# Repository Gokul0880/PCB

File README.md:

View this project on [CADLAB.io](https://cadlab.io/project/28970). 

# PCB Projects

## Overview
This repository contains various PCB designs created using KiCad as part of my learning journey. The projects include different types of power converters, sensor modules, and other embedded system circuits.

## Included Designs
- **Buck Converter** - Step-down DC-DC converter
- **Boost Converter** - Step-up DC-DC converter
- **Linear Regulators** - Voltage regulation circuits
- **Power Management Circuits** - Various power distribution designs
- **Sensor Modules** - PCB layouts for different sensors

## Project Structure
```
📂 project_root/
 ├── 📁 buck_converter/   # Buck converter design files
 ├── 📁 boost_converter/  # Boost converter design files
 ├── 📁 regulators/       # Linear regulator PCB files
 ├── 📁 sensor_modules/   # Various sensor module PCB designs
 ├── 📁 gerber_files/     # Manufacturing-ready Gerber files
 ├── 📁 bom/              # Bill of Materials (BOM)
 ├── 📁 3d_models/        # 3D models for components
 ├── 📁 documentation/    # Datasheets, design notes, etc.
 ├── README.md           # Project overview (this file)
```

## Installation & Usage
1. Clone the repository:
   ```sh
   git clone https://github.com/yourusername/your-pcb-repo.git
   ```
2. Open the project in KiCad:
   - Open KiCad and load the required `.pro` file.
   - Access the schematic editor and PCB layout as needed.
3. Generate Gerber files for manufacturing:
   - Use KiCad's "Plot" function to export Gerber files.

## Bill of Materials (BOM)
Each project folder contains a BOM listing all components used in the design.

## Contribution
Feel free to fork this repository and submit pull requests for improvements or modifications.

## License
This project is licensed under the MIT License - see the LICENSE file for details.

## Author
Gokula Kannan R

For any questions or collaborations, contact me at [gokul567gd@gmail.com].

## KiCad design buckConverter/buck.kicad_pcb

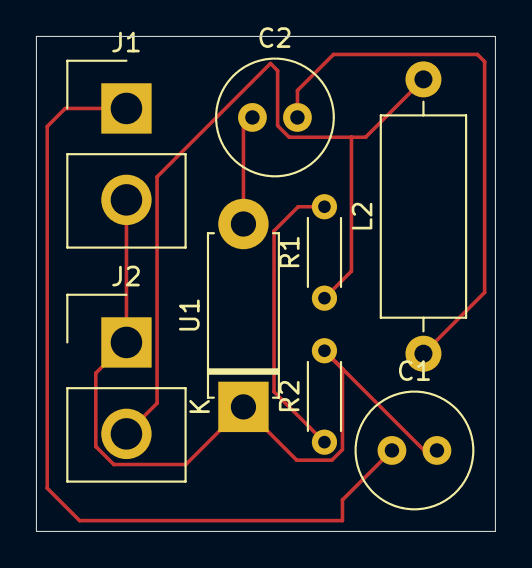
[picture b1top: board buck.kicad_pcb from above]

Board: 2 copper layers, 25.5 x 27.5 mm, 8 parts (0 on the bottom side), 6 nets.

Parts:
C1: C; C_Radial_D6.3mm_H5.0mm_P2.50mm
C2: C; C_Radial_D6.3mm_H11.0mm_P2.50mm
J1, J2: IN; Samtec_HPM-02-01-x-S_Straight_1x02_Pitch5.08mm
L2: SPM3015T-4R7M-LR; L_Axial_L11.0mm_D4.5mm_P15.24mm_Horizontal_Fastron_MECC
R1, R2: R_US; R_Axial_DIN0204_L3.6mm_D1.6mm_P5.08mm_Horizontal
U1: TPS561208DDCR; D_5W_P10.16mm_Horizontal

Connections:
/IN: C1.1, J1.1
/VBST: C2.1, U1.2 (SW)
GND: C1.2, J1.2, J2.1, R2.2, U1.1 (GND)
unnamed: C2.2, L2.1
unnamed: J2.2, L2.2, R1.1
unnamed: R1.2, R2.1

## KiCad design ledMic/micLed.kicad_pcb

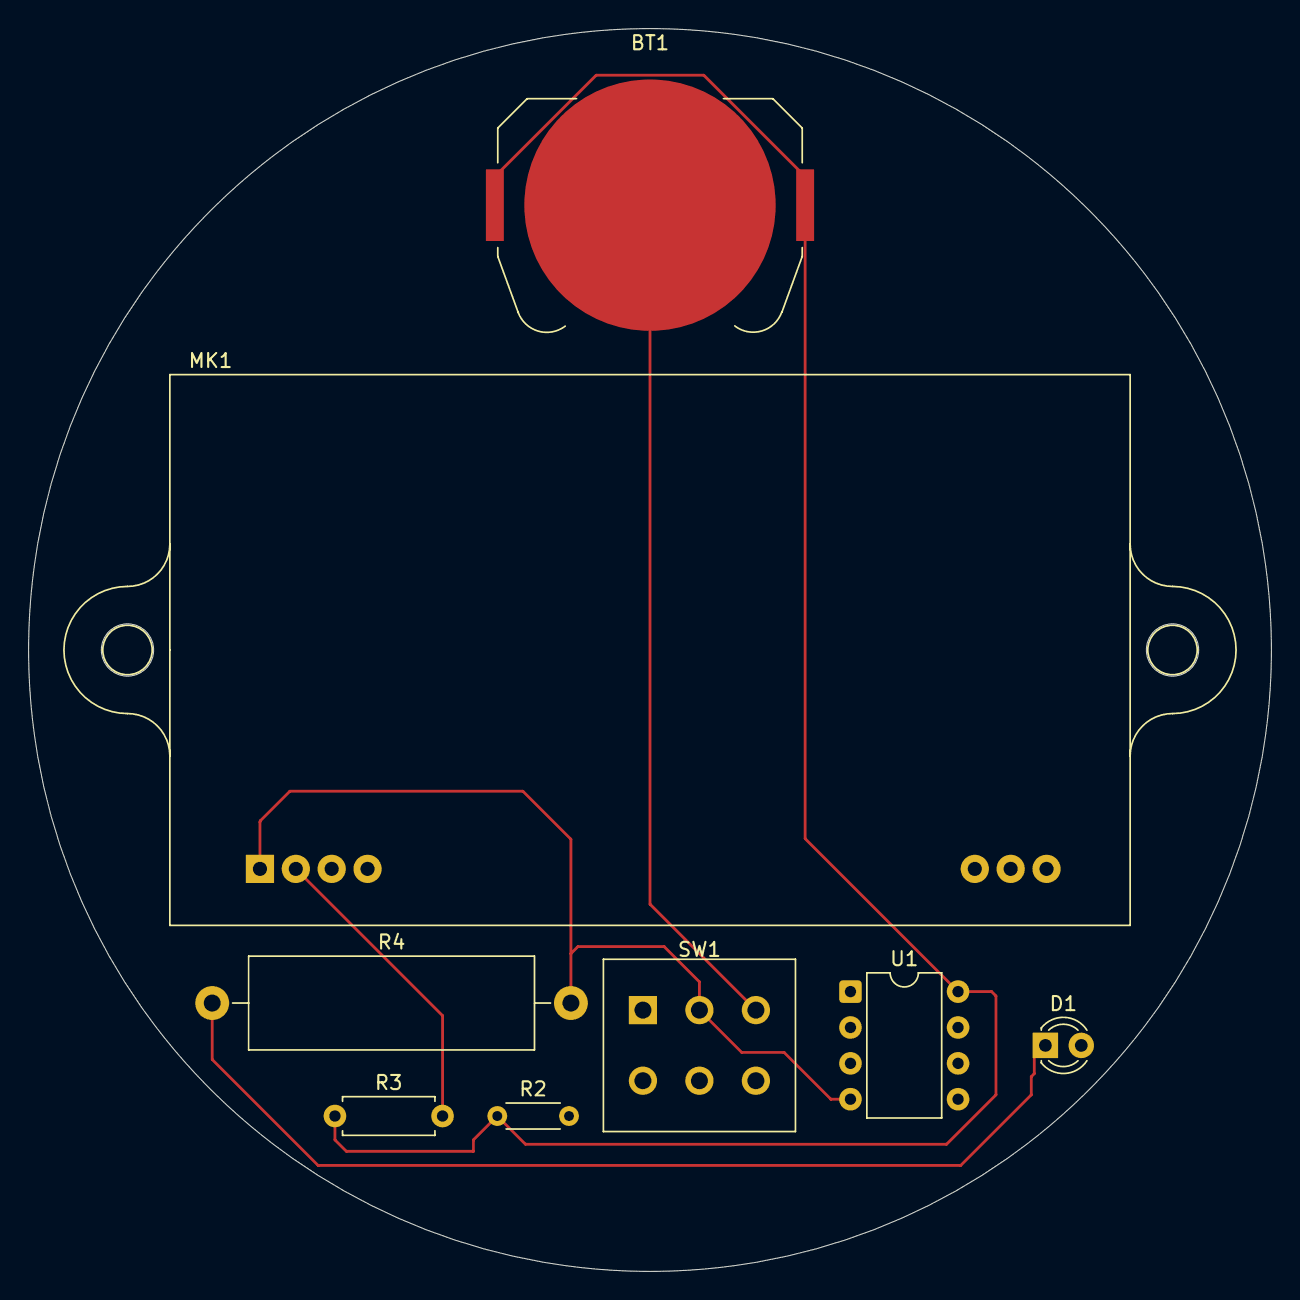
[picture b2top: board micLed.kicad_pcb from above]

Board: 2 copper layers, 88.0 x 88.0 mm, 8 parts (0 on the bottom side), 5 nets.

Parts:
BT1: 3.3v cell; BatteryHolder_Keystone_3034_1x20mm
D1: LED; LED_D3.0mm_Clear
MK1: Microphone; Reverb_BTDR-1H
R2: 10k; R_Axial_DIN0204_L3.6mm_D1.6mm_P5.08mm_Horizontal
R3: R; R_Axial_DIN0207_L6.3mm_D2.5mm_P7.62mm_Horizontal
R4: 470; R_Axial_Power_L20.0mm_W6.4mm_P25.40mm
SW1: SW_DPDT_x2; SW_PUSH_E-Switch_FS5700DP_DPDT
U1: ATtiny85V-10P; DIP-8_W7.62mm

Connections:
GND: MK1.1 (-), R4.2, SW1.2 (B), U1.4 (GND)
unnamed: BT1.2 (-), SW1.3 (C)
unnamed: D1.1 (K), R4.1
unnamed: MK1.2 (+), R3.2
VCC: BT1.1 (+), R2.1, R3.1, U1.8 (VCC)

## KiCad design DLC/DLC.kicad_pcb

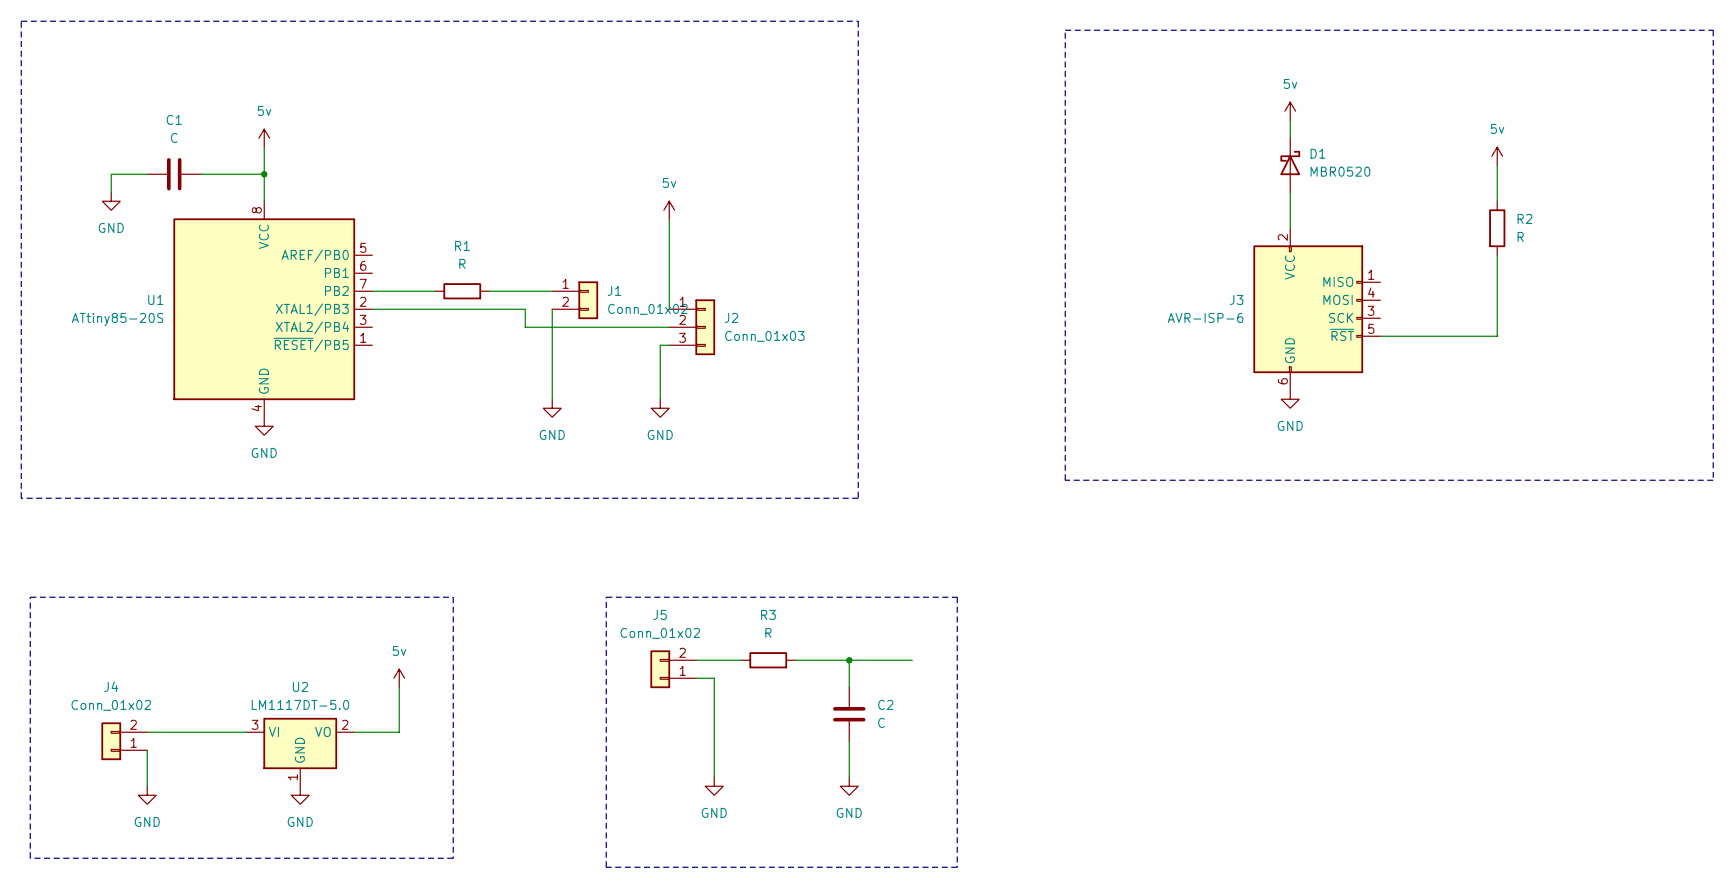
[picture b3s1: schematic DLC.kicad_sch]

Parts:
C1, C2: C; C_Axial_L5.1mm_D3.1mm_P12.50mm_Horizontal
D1: MBR0520; D_SOD-123
J1, J4, J5: Conn_01x02; PinHeader_1x02_P2.54mm_Horizontal
J2: Conn_01x03; PinHeader_1x03_P2.54mm_Horizontal
J3: AVR-ISP-6; IDC-Header_2x03_P2.54mm_Horizontal
R1, R2, R3: R; R_Axial_DIN0207_L6.3mm_D2.5mm_P7.62mm_Horizontal
U1: ATtiny85-20S; SOIC-8_5.3x5.3mm_P1.27mm
U2: LM1117DT-5.0; TO-252-3_TabPin2

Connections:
5v: C1.2, D1.1 (K), J2.1, R2.1, U1.8 (VCC), U2.2 (VO)
GND: C1.1, C2.2, J1.2, J2.3, J3.6 (GND), J4.1, J5.1, U1.4 (GND), U2.1 (GND)
unnamed: C2.1, R3.2
unnamed: D1.2 (A), J3.2 (VCC)
unnamed: J1.1, R1.2
unnamed: J2.2, U1.2 (XTAL1/PB3)
unnamed: J3.5 (~RST), R2.2
unnamed: J4.2, U2.3 (VI)
unnamed: J5.2, R3.1
unnamed: R1.1, U1.7 (PB2)

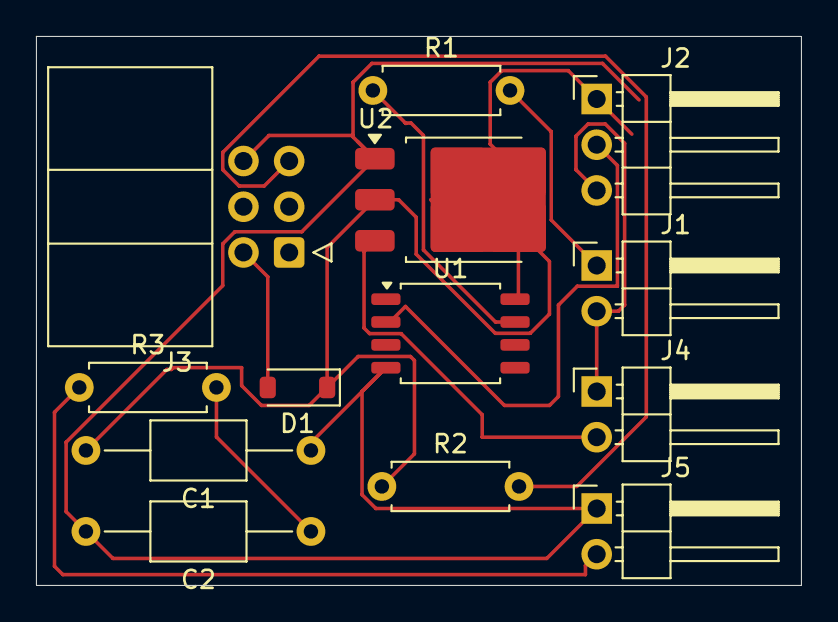
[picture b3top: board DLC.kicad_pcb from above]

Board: 2 copper layers, 42.5 x 30.5 mm, 13 parts (0 on the bottom side), 10 nets.

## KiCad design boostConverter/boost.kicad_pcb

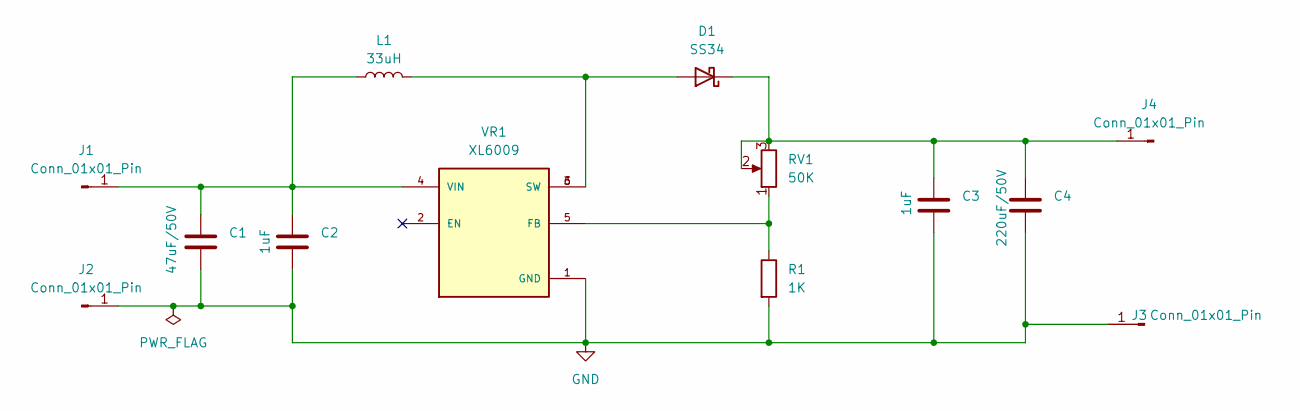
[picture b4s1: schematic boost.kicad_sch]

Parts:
C1: 47uF/50V; C_Radial_D6.3mm_H11.0mm_P2.50mm
C2, C3: 1uF; C_Radial_D5.0mm_H11.0mm_P2.00mm
C4: 220uF/50V; C_Axial_L12.0mm_D8.5mm_P20.00mm_Horizontal
D1: SS34; D_SMA
J1, J2, J3, J4: Conn_01x01_Pin; PinHeader_1x01_P2.54mm_Horizontal
L1: 33uH; L_Axial_L26.0mm_D9.0mm_P30.48mm_Horizontal_Fastron_77A
R1: 1K; R_Axial_DIN0207_L6.3mm_D2.5mm_P10.16mm_Horizontal
RV1: 50K; Potentiometer_Bourns_3296W_Vertical
VR1: XL6009; DPAK170P1435X465-6N; PARTREV 1.1

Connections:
GND: C1.2, C2.1, C3.2, C4.2, J2.1, J3.1, R1.2, VR1.1 (GND)
unnamed: D1.2 (A), L1.2, VR1.3 (SW), VR1.6 (SW)
unnamed: C3.1, C4.1, D1.1 (K), J4.1, RV1.2, RV1.3
unnamed: C1.1, C2.2, J1.1, L1.1, VR1.4 (VIN)
unnamed: R1.1, RV1.1, VR1.5 (FB)

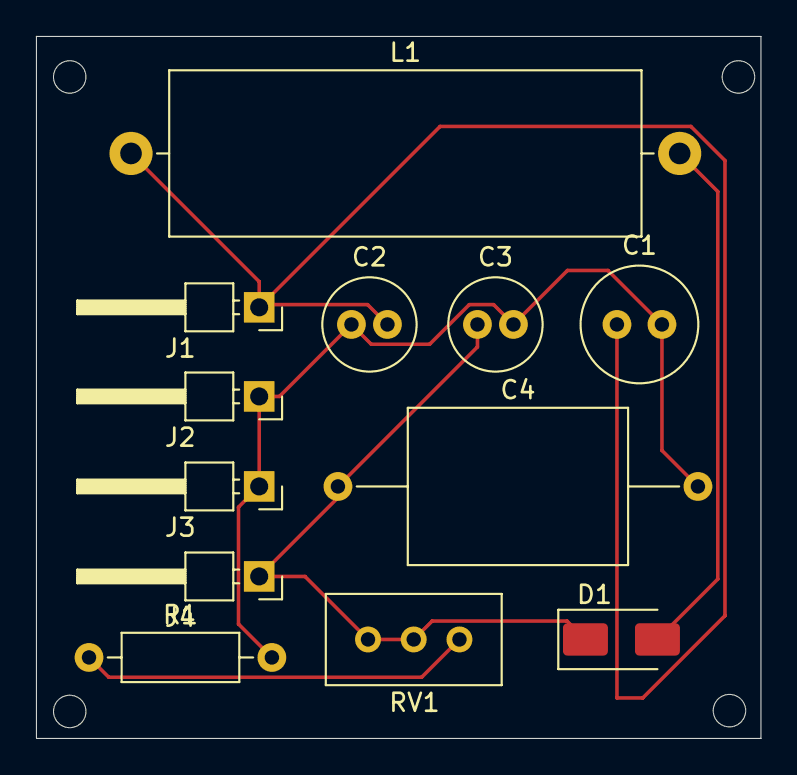
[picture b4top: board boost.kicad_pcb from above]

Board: 2 copper layers, 40.2 x 39.0 mm, 12 parts (0 on the bottom side), 5 nets.

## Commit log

2025-03-21 Backlink to CADLAB.io has been added.
